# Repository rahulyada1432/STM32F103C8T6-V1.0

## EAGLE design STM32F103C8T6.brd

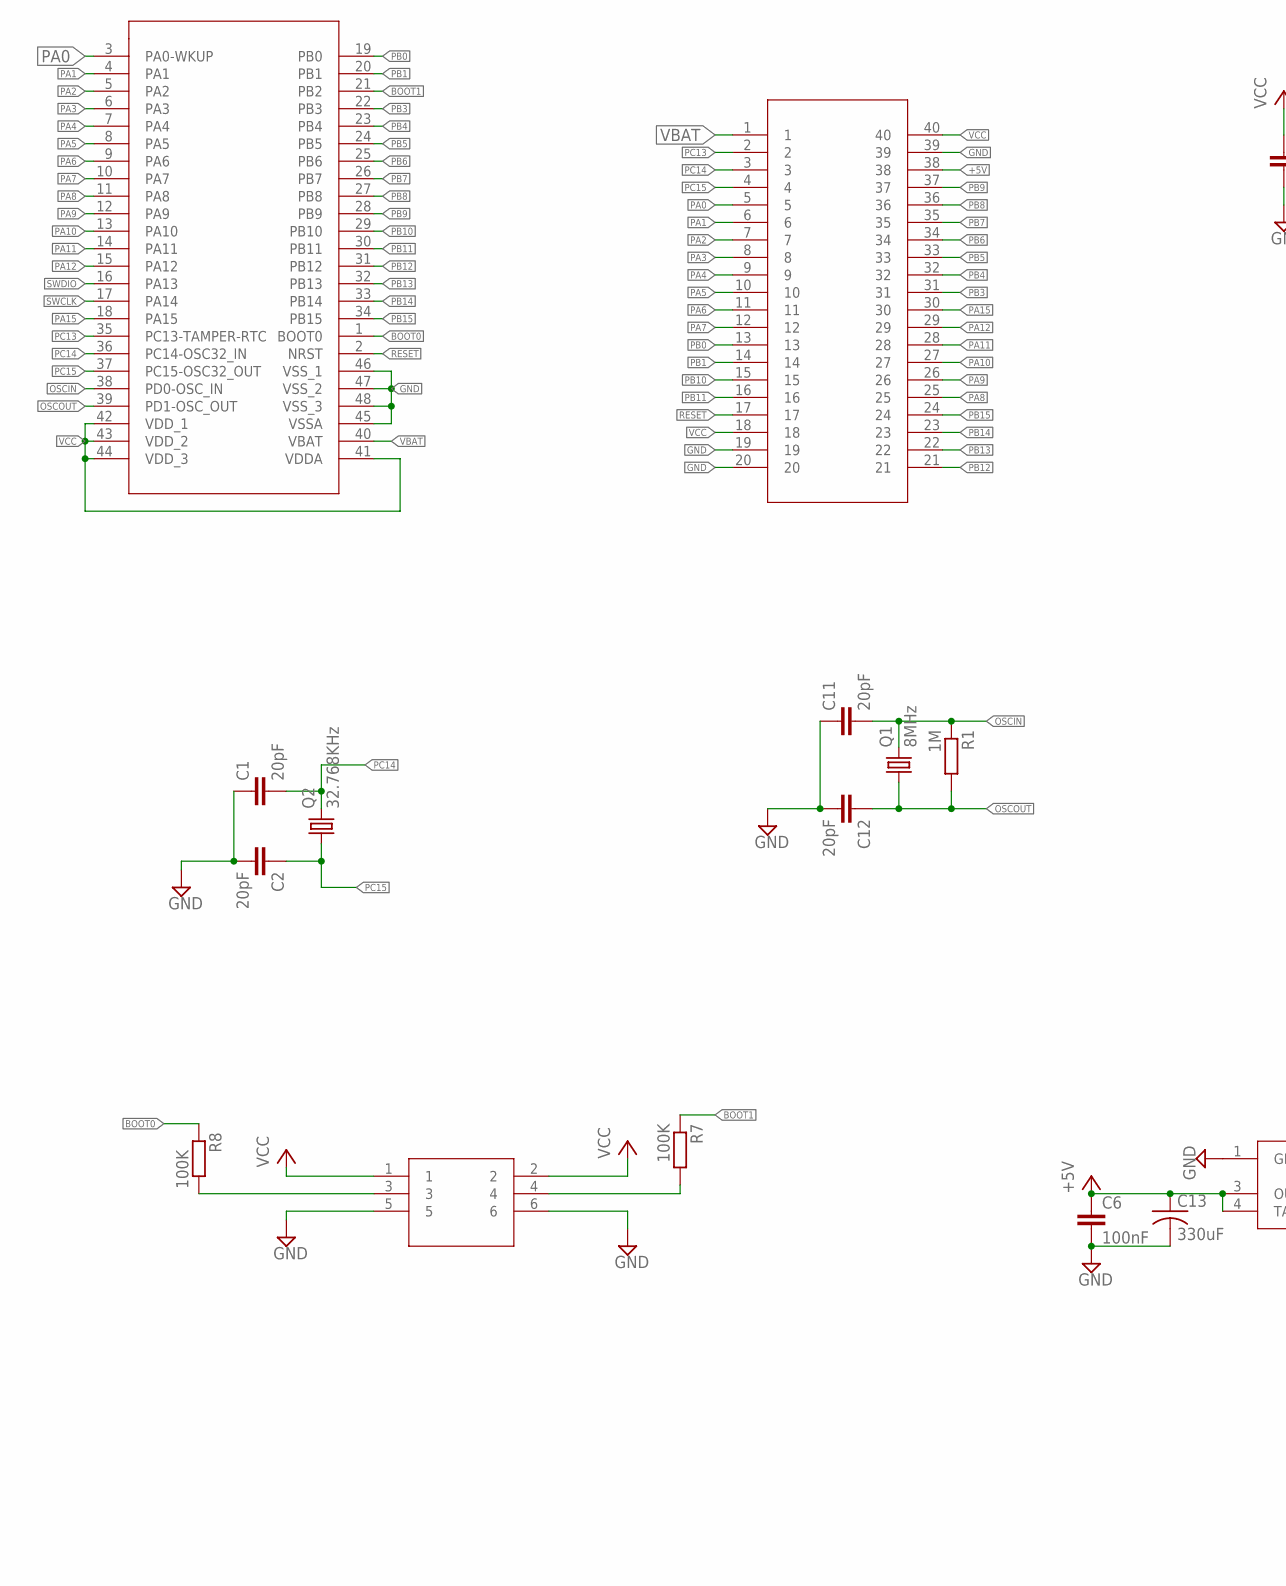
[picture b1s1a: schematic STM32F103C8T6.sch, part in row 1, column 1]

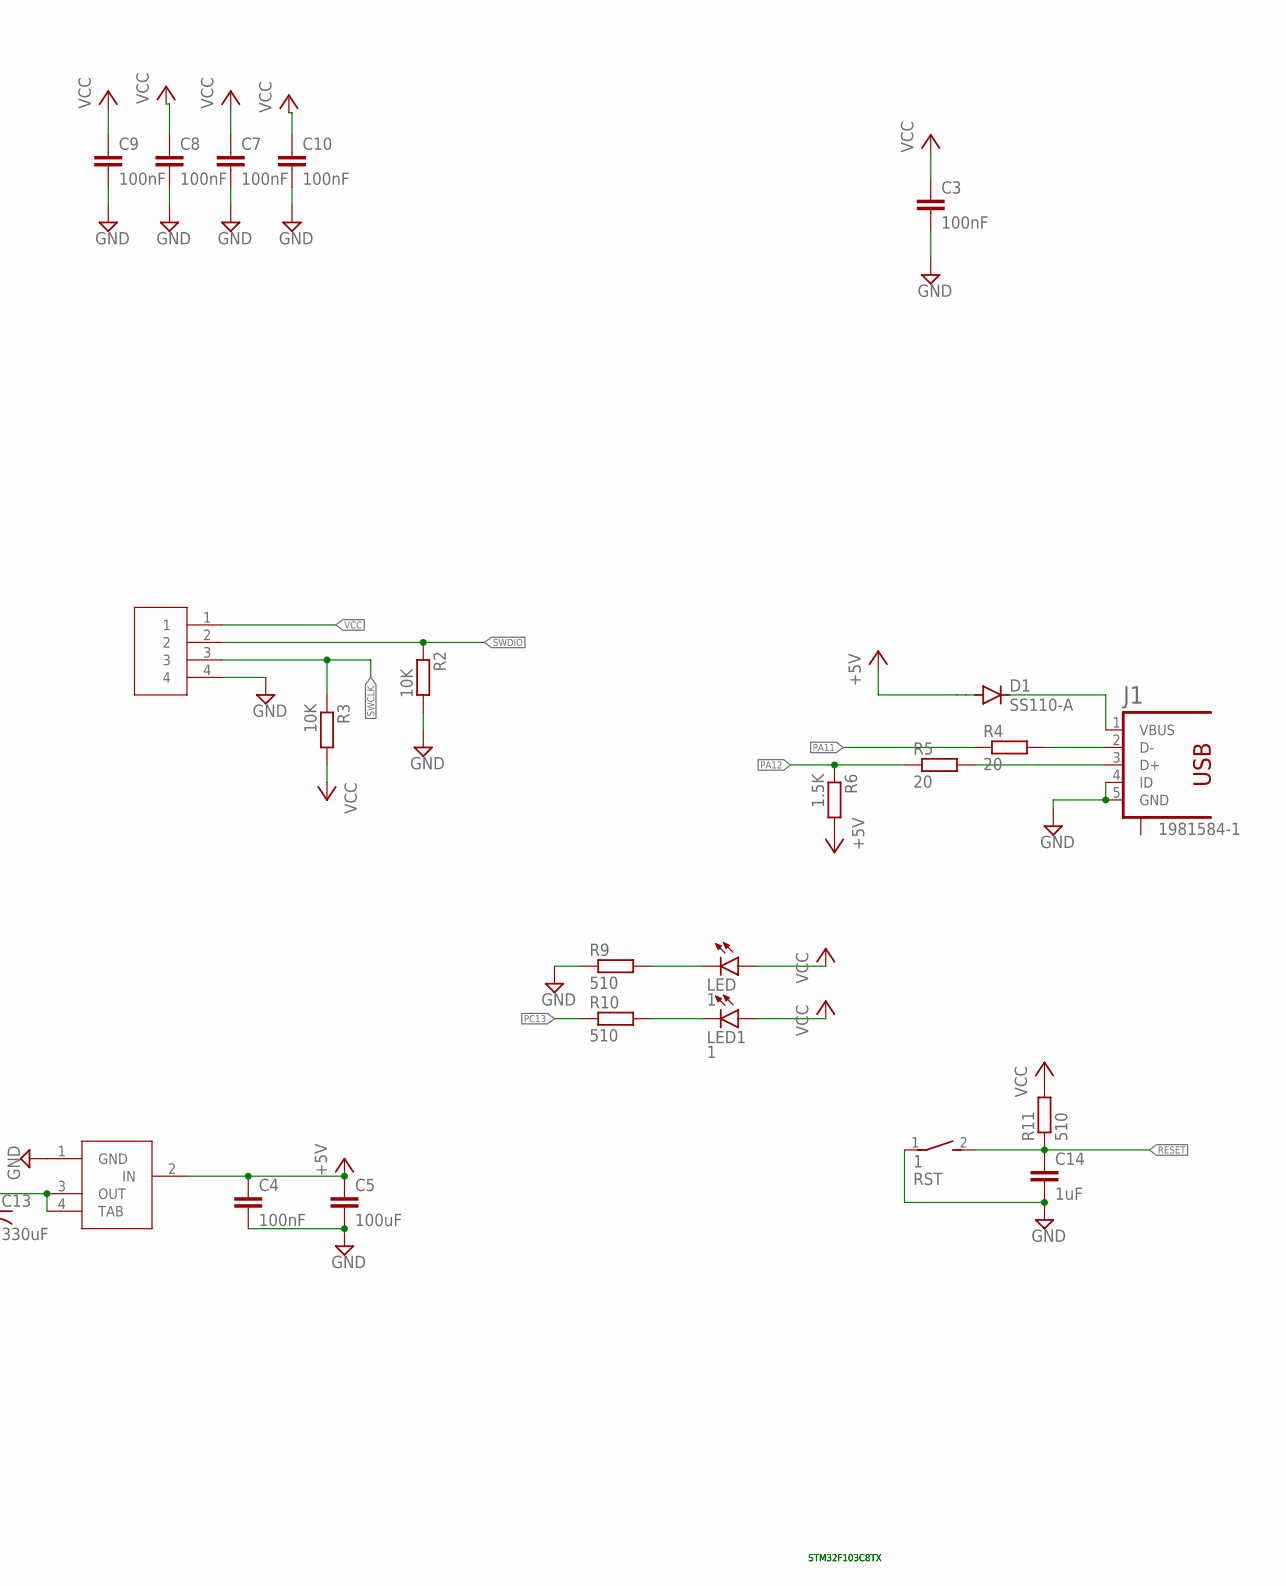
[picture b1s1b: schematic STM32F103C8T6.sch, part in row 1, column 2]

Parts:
1: RST; DS-01
C1, C2, C11, C12: 20pF; C025-024X044
C3, C4, C6, C7, C8, C9, C10: 100nF; C025-024X044
C5: 100uF; C025-024X044
C13: 330uF; C050-024X044
C14: 1uF; C025-024X044
D1: SS110-A; D-2.5
J1: 1981584-1
LED, LED1: 1; LED3MM
Q1: 8MHz; SM49
Q2: 32.768KHz; SM49
R1: 1M; 0204V
R2, R3: 10K; 0204V
R4, R5: 20; 0204V
R6: 1.5K; 0204V
R7, R8: 100K; 0204V
R9, R10, R11: 510; 0204V
U$1: STM32F103C8T6; QFP50P1290X1290X120-48N
U$2: GPINS; HDRV40W64P254_20X2_1016X508X838B
U$4: PLATE; HDRV4W64P254_1X4_1016X508X838B
U$5: IC; DIP762W53P254L500H508Q6B
U$6: SOT223; SOT230P700X180-4N

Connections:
+5V: D1.A, LED.A, LED1.A, R6.2, R11.2, U$2.38
BOOT0: R8.1, U$1.1 (BOOT0)
BOOT1: R7.1, U$1.21 (PB2)
GND: 1.1, C1.1, C2.2, C3.2, C4.2, C5.2, C6.2, C7.2, C8.2, C9.2, C10.2, C11.1, C12.2, C13.2, C14.2, J1.4 (ID), J1.5 (GND), R2.2, R9.1, U$1.45 (VSSA), U$1.46 (VSS_1), U$1.47 (VSS_2), U$1.48 (VSS_3), U$2.19, U$2.20, U$2.39, U$4.4, U$5.5, U$5.6, U$6.1 (GND)
unnamed: D1.C, J1.1 (VBUS)
unnamed: R8.2, U$5.3
unnamed: J1.2 (D-), R4.2
unnamed: R7.2, U$5.4
unnamed: J1.3 (D+), R5.2
unnamed: LED.K (C), R9.2
unnamed: LED1.K (C), R10.2
OSCIN: C11.2, Q1.2, R1.1, U$1.38 (PD0-OSC_IN)
OSCOUT: C12.1, Q1.1, R1.2, U$1.39 (PD1-OSC_OUT)
PA0: U$1.3 (PA0-WKUP), U$2.5
PA1: U$1.4 (PA1), U$2.6
PA2: U$1.5 (PA2), U$2.7
PA3: U$1.6 (PA3), U$2.8
PA4: U$1.7 (PA4), U$2.9
PA5: U$1.8 (PA5), U$2.10
PA6: U$1.9 (PA6), U$2.11
PA7: U$1.10 (PA7), U$2.12
PA8: U$1.11 (PA8), U$2.25
PA9: U$1.12 (PA9), U$2.26
PA10: U$1.13 (PA10), U$2.27
PA11: R4.1, U$1.14 (PA11), U$2.28
PA12: R5.1, R6.1, U$1.15 (PA12), U$2.29
PA15: U$1.18 (PA15), U$2.30
PB0: U$1.19 (PB0), U$2.13
PB1: U$1.20 (PB1), U$2.14
PB3: U$1.22 (PB3), U$2.31
PB4: U$1.23 (PB4), U$2.32
PB5: U$1.24 (PB5), U$2.33
PB6: U$1.25 (PB6), U$2.34
PB7: U$1.26 (PB7), U$2.35
PB8: U$1.27 (PB8), U$2.36
PB9: U$1.28 (PB9), U$2.37
PB10: U$1.29 (PB10), U$2.15
PB11: U$1.30 (PB11), U$2.16
PB12: U$1.31 (PB12), U$2.21
PB13: U$1.32 (PB13), U$2.22
PB14: U$1.33 (PB14), U$2.23
PB15: U$1.34 (PB15), U$2.24
PC13: R10.1, U$1.35 (PC13-TAMPER-RTC), U$2.2
PC14: C1.2, Q2.2, U$1.36 (PC14-OSC32_IN), U$2.3
PC15: C2.1, Q2.1, U$1.37 (PC15-OSC32_OUT), U$2.4
RESET: 1.2, C14.1, R11.1, U$1.2 (NRST), U$2.17
SWCLK: R3.1, U$1.17 (PA14), U$4.3
SWDIO: R2.1, U$1.16 (PA13), U$4.2
VBAT: U$1.40 (VBAT), U$2.1
VCC: C3.1, C4.1, C5.1, C6.1, C7.1, C8.1, C9.1, C10.1, C13.1, R3.2, U$1.41 (VDDA), U$1.42 (VDD_1), U$1.43 (VDD_2), U$1.44 (VDD_3), U$2.18, U$2.40, U$4.1, U$5.1, U$5.2, U$6.2 (IN), U$6.3 (OUT), U$6.4 (TAB)

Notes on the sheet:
STM32F103C8TX

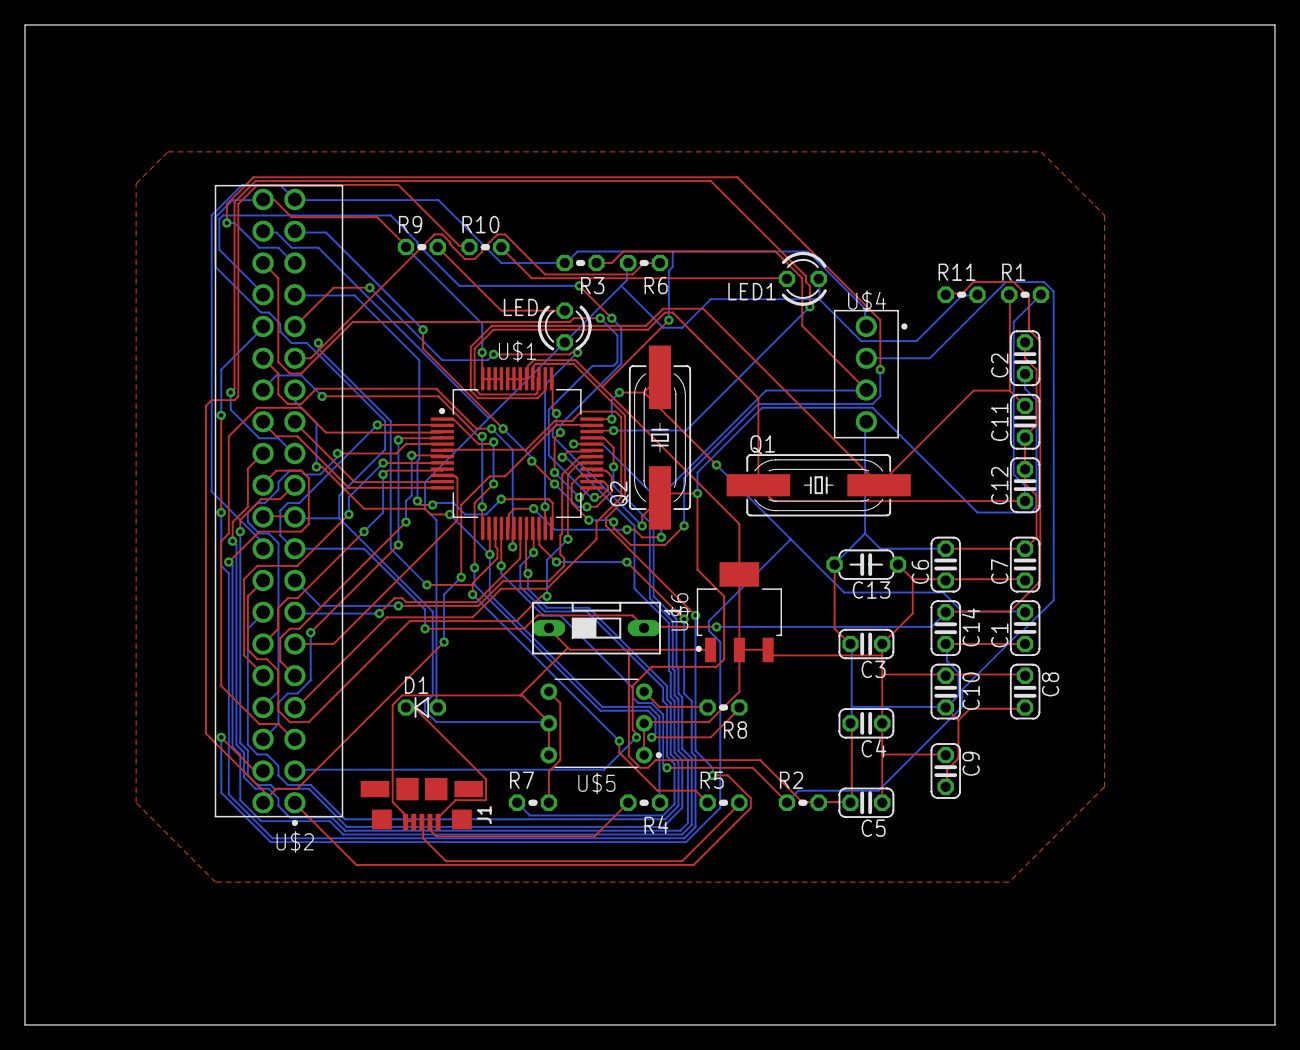
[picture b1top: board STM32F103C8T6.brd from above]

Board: 2 copper layers, 100.0 x 80.0 mm, 37 parts (0 on the bottom side), 50 nets.
